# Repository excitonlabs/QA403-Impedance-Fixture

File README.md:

# QA403 Impedance Fixture

A test fixture for the QuantAsylum QA403 for measuring impedance based on Matt's blog posts:
* https://quantasylum.com/blogs/news/speaker-impedance-measurements
* https://quantasylum.com/blogs/news/measuring-input-impedance

The PCB is fairly flexible, there are three footprints for SMD currents sense resistors and a single through-hole footprint. These are in parallel so the expectation is you place one and write the value on the silk screen space provided. The PCB also had an additional BNC for the L- input which may be useful in push-pull differential measurements.

## Questions

Forum post https://forum.quantasylum.com/t/comments-welcomed-on-test-fixture-pcb-for-impedance-measurements

## How to get this PCB

0. Wait until I confirm everything works (PCBs will arrive this week).
1. Order PCBs from a fab. house such as https://jlcpcb.com or email me I have may spare ones.
2. Order components from the BOM

## BOM

See datasheets in `/Parts` directory.

* Optional 2 x [MKDSN 1,5/ 2-5,08 1729128, terminal block](https://www.phoenixcontact.com/en-us/products/printed-circuit-board-terminal-mkdsn-15-2-508-1729128)
* Optional 2 x [Neutrik NMJ6HCD2, Jack socket](https://www.neutrik.com/en/product/nmj6hcd2)
* 4  x [TE Connectivity 5221123-2, BNC socket](https://www.te.com/usa-en/product-5221123-2.html)
* 1 x current sense resistor of the following types:
  * 2012 (5025)
  * 1206 (3216)
  * 0805 (2012)
  * Through-hole 

## Examples

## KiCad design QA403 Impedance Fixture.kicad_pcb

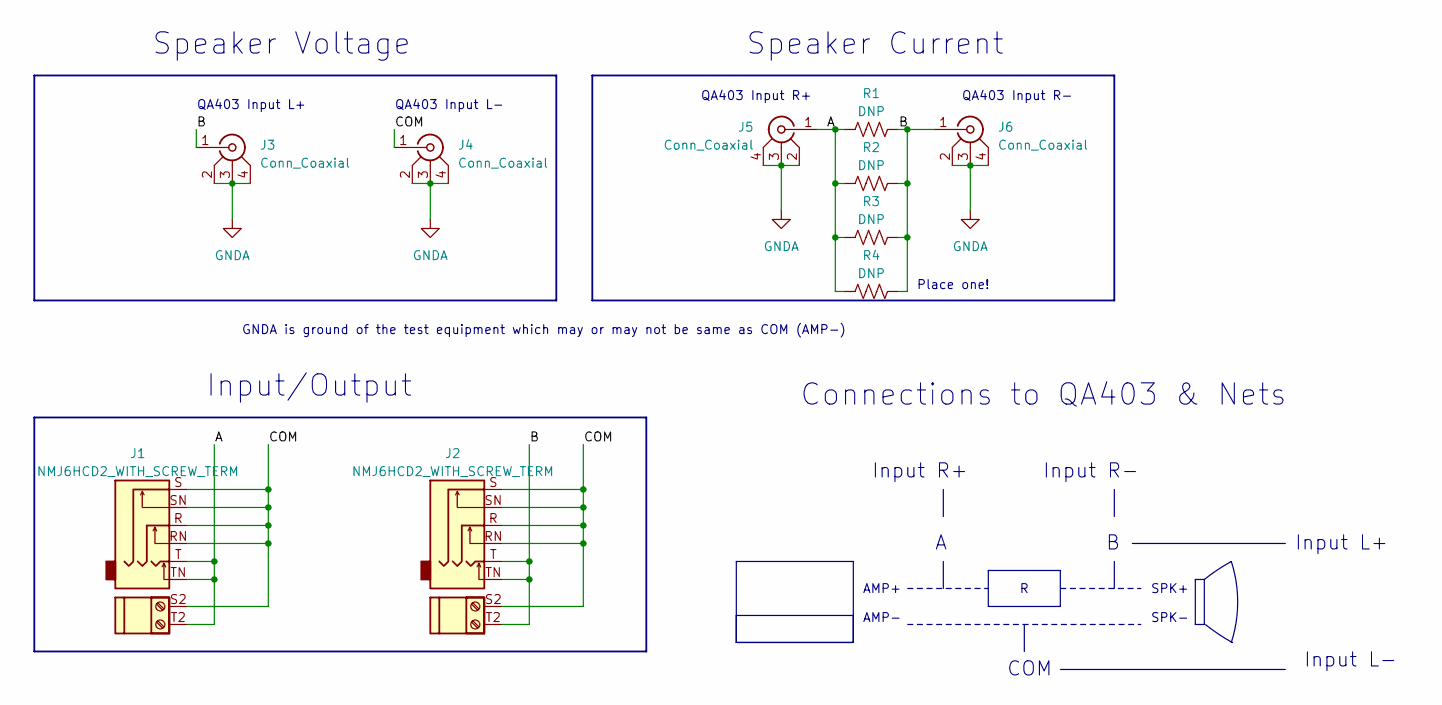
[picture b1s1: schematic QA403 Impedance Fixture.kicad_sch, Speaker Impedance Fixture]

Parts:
J1, J2: NMJ6HCD2_WITH_SCREW_TERM; Dual_Jack_6.35mm_Neutrik_NMJ6HCD2_Horizontal_TerminalBlock_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
J3, J4, J5, J6: Conn_Coaxial; 52211232
R1: DNP; R_2010_5025Metric_Pad1.40x2.65mm_HandSolder
R2: DNP; R_1206_3216Metric_Pad1.30x1.75mm_HandSolder
R3: DNP; R_0805_2012Metric_Pad1.20x1.40mm_HandSolder
R4: DNP; R_Axial_DIN0309_L9.0mm_D3.2mm_P12.70mm_Horizontal

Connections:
/A: J1.T, J1.T2, J1.TN, J5.1 (In), R1.1, R2.1, R3.1, R4.1
/B: J2.T, J2.T2, J2.TN, J3.1 (In), J6.1 (In), R1.2, R2.2, R3.2, R4.2
/COM: J1.R, J1.RN, J1.S, J1.S2, J1.SN, J2.R, J2.RN, J2.S, J2.S2, J2.SN, J4.1 (In)
GNDA: J3.2 (Ext), J3.3 (Ext), J3.4 (Ext), J4.2 (Ext), J4.3 (Ext), J4.4 (Ext), J5.2 (Ext), J5.3 (Ext), J5.4 (Ext), J6.2 (Ext), J6.3 (Ext), J6.4 (Ext)

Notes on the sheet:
Speaker Current
Speaker Voltage
QA403 Input R+
QA403 Input L+
Input L+
GNDA is ground of the test equipment which may or may not be same as COM (AMP-)
Input L-
Input/Output
AMP+ AMP-
Input R-
SPK+ SPK-
Input R+
QA403 Input R-
QA403 Input L-
Connections to QA403 & Nets
COM
Place one!

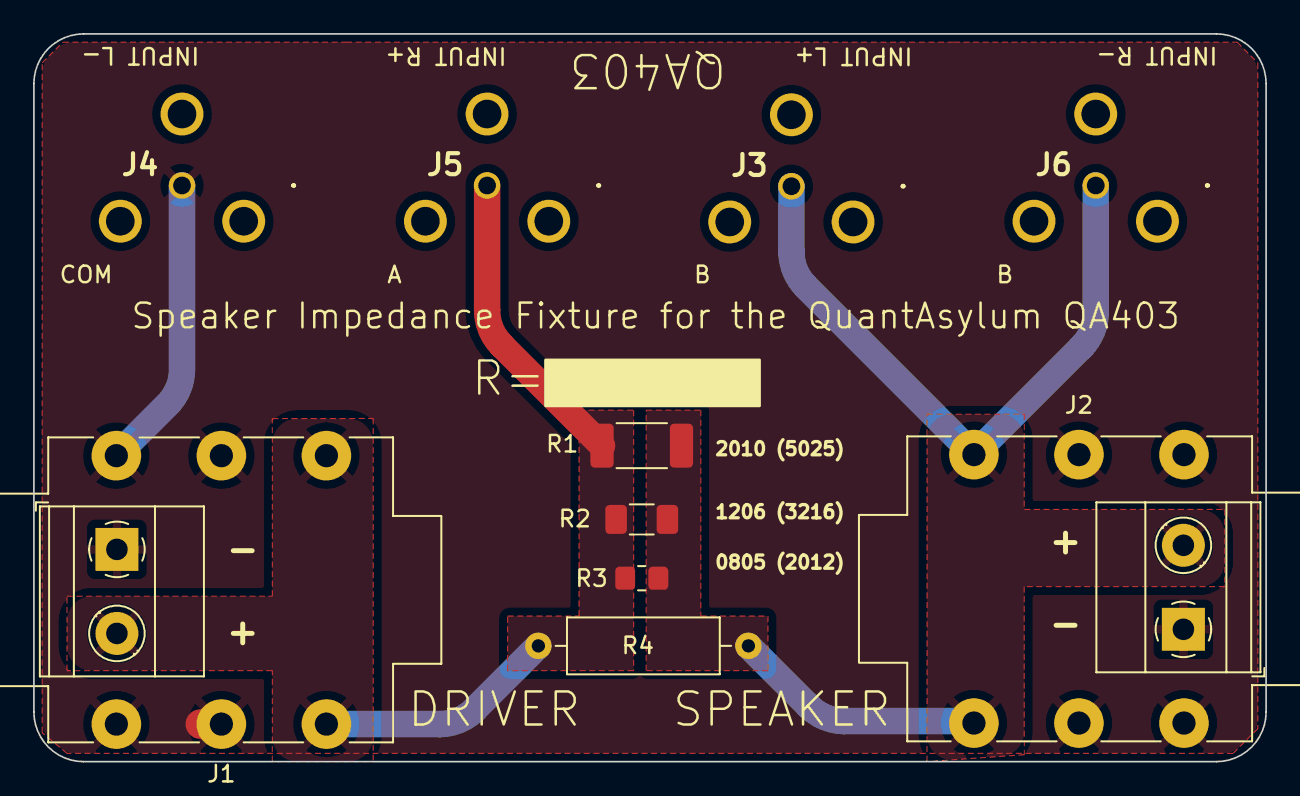
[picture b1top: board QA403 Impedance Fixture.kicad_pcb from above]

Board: 2 copper layers, 74.5 x 44.0 mm, 10 parts (0 on the bottom side), 4 nets.

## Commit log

2023-07-22 Move images to sub folder
2023-08-05 Revision 2 fix error with jack socket connections
    Rev 1 tied jack socket's tip and ring pins together.
    This is OK if you use a stereo plug, but for will short
    signal to ground when using a mono-plug. So a bug.
